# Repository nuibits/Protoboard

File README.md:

# Protoboard
Eurorack/Kosmo powered prototyping boards

## Libraries

Repo uses submodule aoKicad. To clone:

```
git clone git@github.com:holmesrichards/Protoboard.git
git submodule init
git submodule update
```

Alternatively do

```
git clone --recurse-submodules git@github.com:holmesrichards/Protoboard.git
```

Or if you download the repository as a zip file, you must also click on the "aoKicad" and "Kosmo\_panel" links on the GitHub page (they'll have "@ something" after them) and download them as separate zip files which you can unzip into this repo's aoKicad and Kosmo\_panel directories.

If desired, copy the files from aoKicad to wherever you prefer (your KiCad user library directory, for instance, if you have one). Then in KiCad, add symbol library

```
aoKicad/ao_symbols
```
and footprint library
```
aoKicad/ao_tht
```

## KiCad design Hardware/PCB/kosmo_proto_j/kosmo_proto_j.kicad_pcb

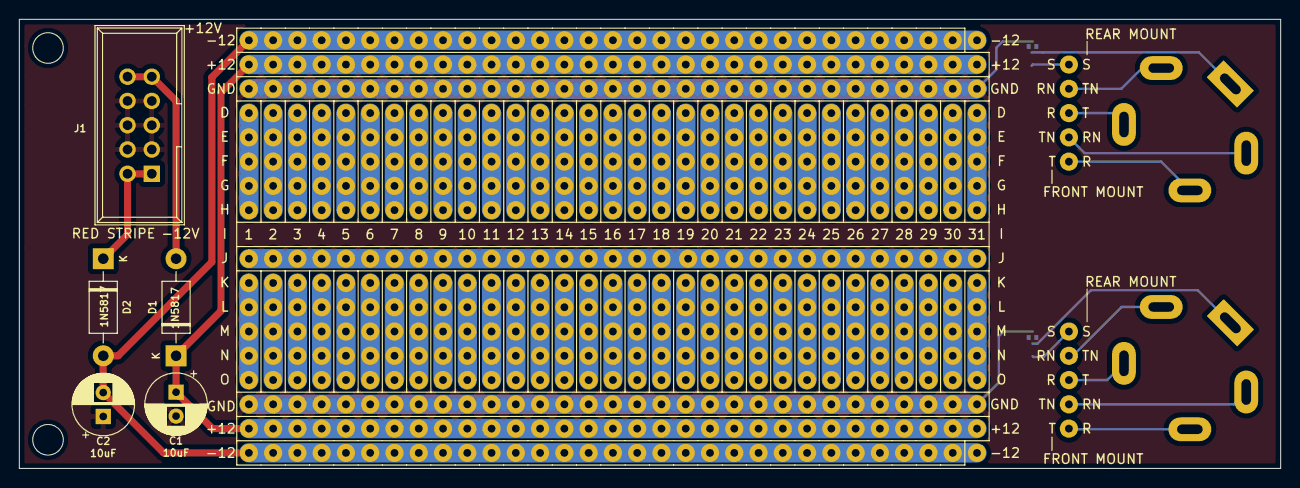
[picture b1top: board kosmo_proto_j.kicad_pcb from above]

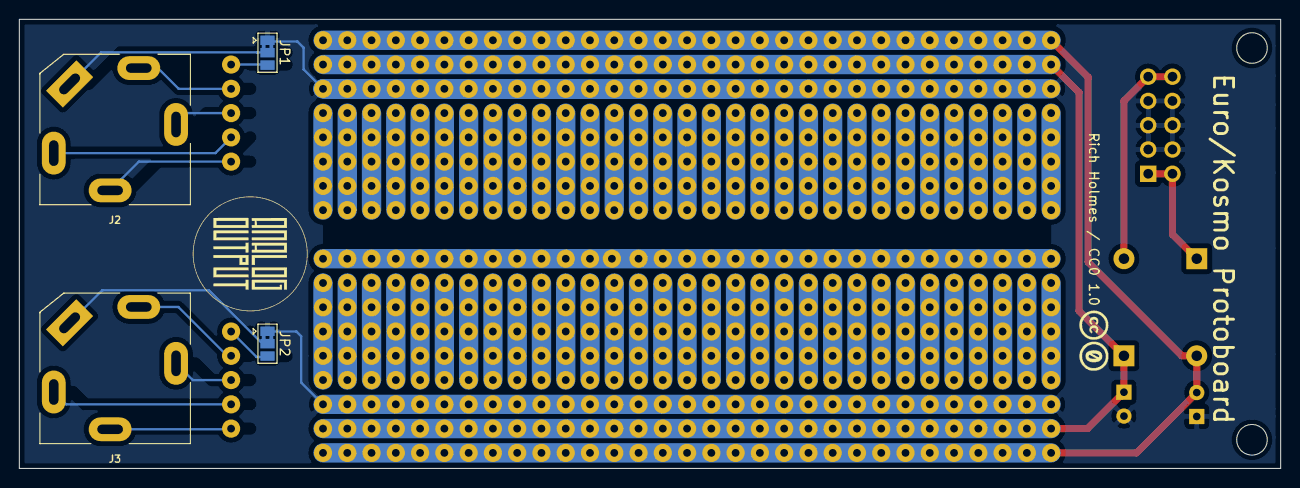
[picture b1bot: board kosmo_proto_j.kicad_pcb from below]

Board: 2 copper layers, 132.0 x 47.0 mm, 550 parts (6 on the bottom side), 80 nets.

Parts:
C1, C2: 10uF; CP_Radial_D6.3mm_P2.50mm
D1, D2: 1N5817; D_DO-41_SOD81_P10.16mm_Horizontal
GRAF1: AO logo; analogoutput_12mm
GRAF2: CC0 logo; CC0_logo
H1, H2: MountingHole; MountingHole_3.2mm_M3
J1: Synth_power_2x5; Power_Header
J2, J3: AudioJack3_SwitchTR; Jack_6.35mm_PJ_629HAN_slots
J4, J5, J6, J7, J8, J9, J10, J11, J12, J13, J14, J15, J16, J17, J18, J19, J20, J21, J22, J23, J24, J25, J26, J27, J28, J29, J30, J31, J32, J33, J34, J35, J36, J37, J38, J39, J40, J41, J42, J43, J44, J45, J46, J47, J48, J49, J50, J51, J52, J53, J54, J55, J56, J57, J58, J59, J60, J61, J62, J63, J64, J65, J66, J67, J68, J69, J70, J71, J72, J73, J74, J75, J76, J77, J78, J79, J80, J81, J82, J83, J84, J85, J86, J87, J88, J89, J90, J91, J92, J93, J94, J95, J96, J97, J98, J99, J100, J101, J102, J103, J104, J105, J106, J107, J108, J109, J110, J111, J112, J113, J114, J115, J116, J117, J118, J119, J120, J121, J122, J123, J124, J125, J126, J127, J128, J129, J130, J131, J132, J133, J134, J135, J136, J137, J138, J139, J140, J141, J142, J143, J144, J145, J146, J147, J148, J149, J150, J151, J152, J153, J154, J155, J156, J157, J158, J159, J160, J161, J162, J163, J164, J165, J166, J167, J168, J169, J170, J171, J172, J173, J174, J175, J176, J177, J178, J179, J180, J181, J182, J183, J184, J185, J186, J187, J188, J189, J190, J191, J192, J193, J194, J195, J196, J197, J198, J199, J200, J201, J202, J203, J204, J205, J206, J207, J208, J209, J210, J211, J212, J213, J214, J215, J216, J217, J218, J219, J220, J221, J222, J223, J224, J225, J226, J227, J228, J229, J230, J231, J232, J233, J234, J235, J236, J237, J238, J239, J240, J241, J242, J243, J244, J245, J246, J247, J248, J249, J250, J251, J252, J253, J254, J255, J256, J257, J258, J259, J260, J261, J262, J263, J264, J265, J266, J267, J268, J269, J270, J271, J272, J273, J274, J275, J276, J277, J278, J279, J280, J281, J282, J283, J284, J285, J286, J287, J288, J289, J290, J291, J292, J293, J294, J295, J296, J297, J298, J299, J300, J301, J302, J303, J304, J305, J306, J307, J308, J309, J310, J311, J312, J313, J314, J315, J316, J317, J318, J319, J320, J321, J322, J323, J324, J325, J326, J327, J328, J329, J330, J331, J332, J333, J334, J335, J336, J337, J338, J339, J340, J341, J342, J343, J344, J345, J346, J347, J348, J349, J350, J351, J352, J353, J354, J355, J356, J357, J358, J359, J360, J361, J362, J363, J364, J365, J366, J367, J368, J369, J370, J371, J372, J373, J374, J375, J376, J377, J378, J379, J380, J381, J382, J383, J384, J385, J386, J387, J388, J389, J390, J391, J392, J393, J394, J395, J396, J397, J398, J399, J400, J401, J402, J403, J404, J405, J406, J407, J408, J409, J410, J411, J412, J413, J414, J415, J416, J417, J418, J419, J420, J421, J422, J423, J424, J425, J426, J427, J428, J429, J430, J431, J432, J433, J434, J435, J436, J437, J438, J439, J440, J441, J442, J443, J444, J445, J446, J447, J448, J449, J450, J451, J452, J453, J454, J455, J456, J457, J458, J459, J460, J461, J462, J463, J464, J465, J466, J467, J468, J469, J470, J471, J472, J473, J474, J475, J476, J477, J478, J479, J480, J481, J482, J483, J484, J485, J486, J487, J488, J489, J490, J491, J492, J493, J494, J495, J496, J497, J498, J499, J500, J501, J502, J503, J504, J505, J506, J507, J508, J509, J510, J511, J512, J513, J514, J515, J516, J517, J518, J519, J520, J521, J522, J523, J524, J525, J526, J527, J528, J529, J530, J531, J532, J533, J534, J535, J536, J537, J538, J539, J540: 1x1; Perf_Board_Hole
JP1, JP2: SolderJumper_3_Bridged12; SolderJumper-3_P1.3mm_Bridged2Bar12_Pad1.0x1.5mm

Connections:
+12V: C1.1, D1.1, J5.1, J13.1, J21.1, J29.1, J37.1, J45.1, J53.1, J61.1, J69.1, J77.1, J85.1, J93.1, J101.1, J109.1, J117.1, J125.1, J133.1, J141.1, J149.1, J157.1, J165.1, J173.1, J181.1, J189.1, J197.1, J205.1, J213.1, J221.1, J229.1, J237.1, J245.1, J269.1, J278.1, J287.1, J296.1, J305.1, J314.1, J323.1, J332.1, J341.1, J350.1, J359.1, J368.1, J377.1, J386.1, J395.1, J404.1, J413.1, J422.1, J431.1, J440.1, J449.1, J458.1, J467.1, J476.1, J485.1, J494.1, J503.1, J512.1, J521.1, J530.1, J539.1
-12V: C2.2, D2.2, J4.1, J12.1, J20.1, J28.1, J36.1, J44.1, J52.1, J60.1, J68.1, J76.1, J84.1, J92.1, J100.1, J108.1, J116.1, J124.1, J132.1, J140.1, J148.1, J156.1, J164.1, J172.1, J180.1, J188.1, J196.1, J204.1, J212.1, J220.1, J228.1, J236.1, J244.1, J270.1, J279.1, J288.1, J297.1, J306.1, J315.1, J324.1, J333.1, J342.1, J351.1, J360.1, J369.1, J378.1, J387.1, J396.1, J405.1, J414.1, J423.1, J432.1, J441.1, J450.1, J459.1, J468.1, J477.1, J486.1, J495.1, J504.1, J513.1, J522.1, J531.1, J540.1
GND: C1.2, C2.1, J1.3, J1.4, J1.5, J1.6, J1.7, J1.8, J6.1, J14.1, J22.1, J30.1, J38.1, J46.1, J54.1, J62.1, J70.1, J78.1, J86.1, J94.1, J102.1, J110.1, J118.1, J126.1, J134.1, J142.1, J150.1, J158.1, J166.1, J174.1, J182.1, J190.1, J198.1, J206.1, J214.1, J222.1, J230.1, J238.1, J246.1, J268.1, J277.1, J286.1, J295.1, J304.1, J313.1, J322.1, J331.1, J340.1, J349.1, J358.1, J367.1, J376.1, J385.1, J394.1, J403.1, J412.1, J421.1, J430.1, J439.1, J448.1, J457.1, J466.1, J475.1, J484.1, J493.1, J502.1, J511.1, J520.1, J529.1, J538.1, JP1.1, JP2.1
unnamed: D1.2, J1.9, J1.10
unnamed: D2.1, J1.1, J1.2
unnamed: J2.R, J252.1
unnamed: J2.RN, J256.1
unnamed: J2.S, JP1.2
unnamed: J2.T, J253.1
unnamed: J2.TN, J257.1
unnamed: J3.S, JP2.2
unnamed: J7.1, J8.1, J9.1, J10.1, J11.1
unnamed: J15.1, J16.1, J17.1, J18.1, J19.1
unnamed: J23.1, J24.1, J25.1, J26.1, J27.1
unnamed: J31.1, J32.1, J33.1, J34.1, J35.1
unnamed: J39.1, J40.1, J41.1, J42.1, J43.1
unnamed: J47.1, J48.1, J49.1, J50.1, J51.1
unnamed: J55.1, J56.1, J57.1, J58.1, J59.1
unnamed: J63.1, J64.1, J65.1, J66.1, J67.1
unnamed: J71.1, J72.1, J73.1, J74.1, J75.1
unnamed: J79.1, J80.1, J81.1, J82.1, J83.1
unnamed: J87.1, J88.1, J89.1, J90.1, J91.1
unnamed: J95.1, J96.1, J97.1, J98.1, J99.1
unnamed: J103.1, J104.1, J105.1, J106.1, J107.1
unnamed: J111.1, J112.1, J113.1, J114.1, J115.1
unnamed: J119.1, J120.1, J121.1, J122.1, J123.1
unnamed: J127.1, J128.1, J129.1, J130.1, J131.1
unnamed: J135.1, J136.1, J137.1, J138.1, J139.1
unnamed: J143.1, J144.1, J145.1, J146.1, J147.1
unnamed: J151.1, J152.1, J153.1, J154.1, J155.1
unnamed: J159.1, J160.1, J161.1, J162.1, J163.1
unnamed: J167.1, J168.1, J169.1, J170.1, J171.1
unnamed: J175.1, J176.1, J177.1, J178.1, J179.1
unnamed: J183.1, J184.1, J185.1, J186.1, J187.1
unnamed: J191.1, J192.1, J193.1, J194.1, J195.1
unnamed: J199.1, J200.1, J201.1, J202.1, J203.1
unnamed: J207.1, J208.1, J209.1, J210.1, J211.1
unnamed: J215.1, J216.1, J217.1, J218.1, J219.1
unnamed: J223.1, J224.1, J225.1, J226.1, J227.1
unnamed: J231.1, J232.1, J233.1, J234.1, J235.1
unnamed: J239.1, J240.1, J241.1, J242.1, J243.1
unnamed: J247.1, J248.1, J249.1, J250.1, J251.1
unnamed: J3.R, J254.1
unnamed: J3.T, J255.1
unnamed: J3.RN, J258.1
unnamed: J3.TN, J259.1
unnamed: J260.1, JP1.3
unnamed: J261.1, JP2.3
unnamed: J262.1, J271.1, J280.1, J289.1, J298.1, J307.1, J316.1, J325.1, J334.1, J343.1, J352.1, J361.1, J370.1, J379.1, J388.1, J397.1, J406.1, J415.1, J424.1, J433.1, J442.1, J451.1, J460.1, J469.1, J478.1, J487.1, J496.1, J505.1, J514.1, J523.1, J532.1
unnamed: J263.1, J264.1, J265.1, J266.1, J267.1
unnamed: J272.1, J273.1, J274.1, J275.1, J276.1
unnamed: J281.1, J282.1, J283.1, J284.1, J285.1
unnamed: J290.1, J291.1, J292.1, J293.1, J294.1
unnamed: J299.1, J300.1, J301.1, J302.1, J303.1
unnamed: J308.1, J309.1, J310.1, J311.1, J312.1
unnamed: J317.1, J318.1, J319.1, J320.1, J321.1
unnamed: J326.1, J327.1, J328.1, J329.1, J330.1
unnamed: J335.1, J336.1, J337.1, J338.1, J339.1
unnamed: J344.1, J345.1, J346.1, J347.1, J348.1
unnamed: J353.1, J354.1, J355.1, J356.1, J357.1
unnamed: J362.1, J363.1, J364.1, J365.1, J366.1
unnamed: J371.1, J372.1, J373.1, J374.1, J375.1
unnamed: J380.1, J381.1, J382.1, J383.1, J384.1
unnamed: J389.1, J390.1, J391.1, J392.1, J393.1
unnamed: J398.1, J399.1, J400.1, J401.1, J402.1
unnamed: J407.1, J408.1, J409.1, J410.1, J411.1
unnamed: J416.1, J417.1, J418.1, J419.1, J420.1
unnamed: J425.1, J426.1, J427.1, J428.1, J429.1
unnamed: J434.1, J435.1, J436.1, J437.1, J438.1
unnamed: J443.1, J444.1, J445.1, J446.1, J447.1
unnamed: J452.1, J453.1, J454.1, J455.1, J456.1
unnamed: J461.1, J462.1, J463.1, J464.1, J465.1
unnamed: J470.1, J471.1, J472.1, J473.1, J474.1
unnamed: J479.1, J480.1, J481.1, J482.1, J483.1
unnamed: J488.1, J489.1, J490.1, J491.1, J492.1
unnamed: J497.1, J498.1, J499.1, J500.1, J501.1
unnamed: J506.1, J507.1, J508.1, J509.1, J510.1
unnamed: J515.1, J516.1, J517.1, J518.1, J519.1
unnamed: J524.1, J525.1, J526.1, J527.1, J528.1
unnamed: J533.1, J534.1, J535.1, J536.1, J537.1

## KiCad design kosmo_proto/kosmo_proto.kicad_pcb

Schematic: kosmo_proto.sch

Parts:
C1, C2: 10uF; CP_Radial_D6.3mm_P2.50mm
D1, D2: 1N5817; D_DO-41_SOD81_P7.62mm_Horizontal
GRAF1: AO logo; analogoutput_12mm
GRAF2: CC0 logo; CC0_logo
J1: Synth_power_2x5; Power_Header
J2, J3, J4, J5, J6, J7: Conn_01x01; Perf_Board_Hole

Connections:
+12V: C1.1, D1.1, J2.1, J3.1
-12V: C2.2, D2.2, J6.1, J7.1
GND: C1.2, C2.1, J1.3, J1.4, J1.5, J1.6, J1.7, J1.8, J4.1, J5.1
unnamed: D1.2, J1.9, J1.10
unnamed: D2.1, J1.1, J1.2

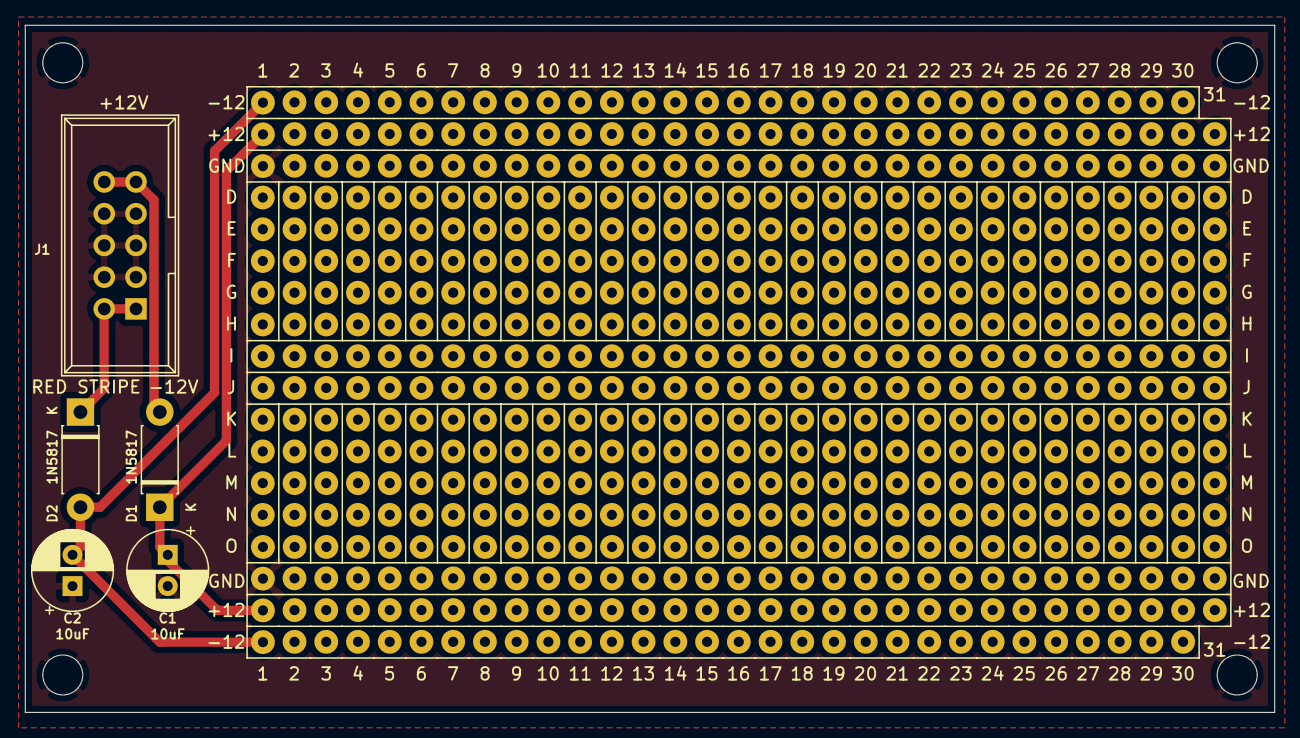
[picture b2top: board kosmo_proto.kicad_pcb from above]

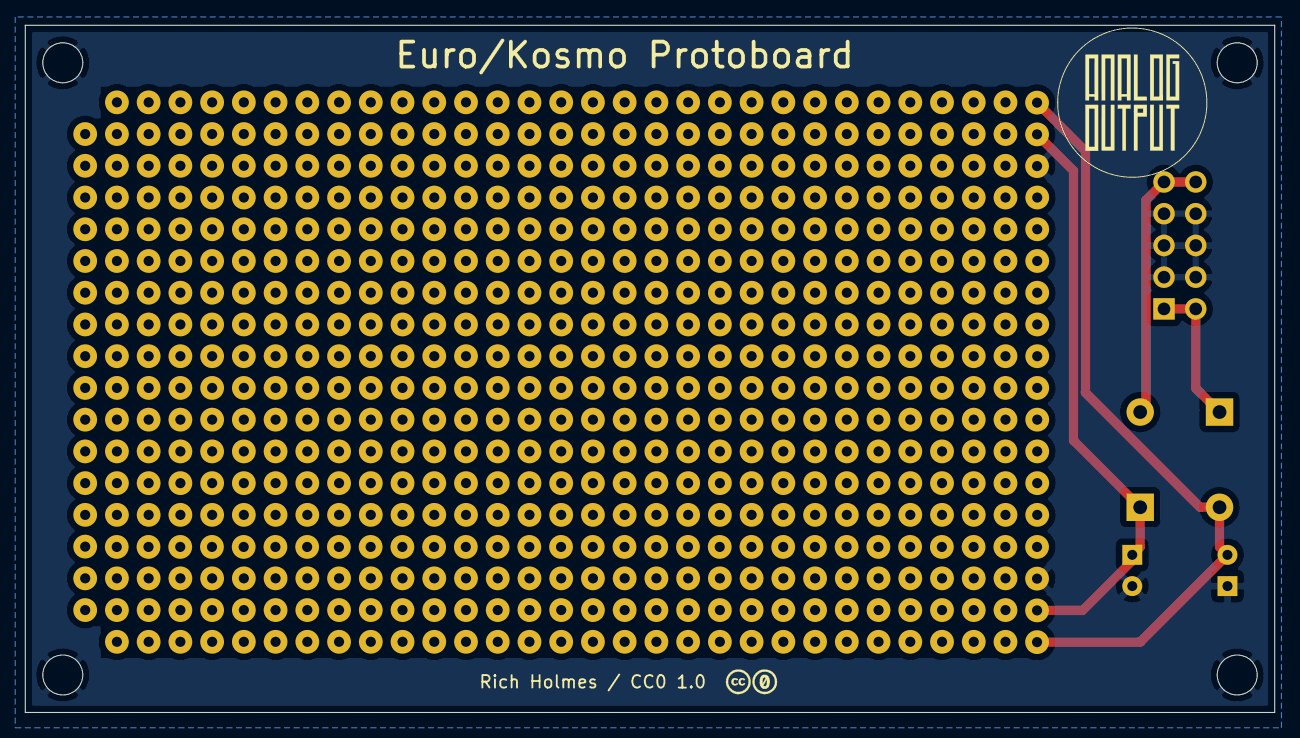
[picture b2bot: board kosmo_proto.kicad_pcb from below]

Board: 2 copper layers, 100.0 x 55.0 mm, 13 parts (2 on the bottom side), 5 nets.

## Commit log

2020-09-04 Initial version
2020-09-04 .gitignore
2020-09-16 Replace fuses with diodes; improve layout; add row/column identifiers
2020-10-25 Final design for second run
2020-12-01 Fix typo
2021-01-02 Footprints updated
2021-01-17 Include lib table files
2021-02-19 Footprint update
2021-02-28 Update .gitignore, DIN5
2021-04-30 Dupe numbers and letters; add text/logo; change cap footprints; size and positioning tweaks
2021-08-07 New Gerbers
2021-08-12 pcb tweak
2021-08-16 Rework layout
2021-08-21 relocate libraries
2021-08-21 rm project libraries
2021-08-27 submodule doc
2021-08-29 Narrower version with jacks (kosmo_proto_j)
2021-09-07 Jack labels; images
2021-09-15 more jacks mod, tweak original

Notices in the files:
Hardware/PCB/kosmo_proto_j/kosmo_proto_j.kicad_pcb:
Rich Holmes / CC0 1.0
